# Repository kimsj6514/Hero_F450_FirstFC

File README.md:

# STM32F765 기반 커스텀 드론 비행 컨트롤러(FC) 개발

**현장 경험을 바탕으로 안정성과 신뢰성을 확보한 고성능 드론 FC를 직접 설계하고 개발하는 개인 프로젝트입니다.**

## 📖 프로젝트 소개
기성품 FC의 한계를 넘어, 특정 임무(정밀 비행, 안정적인 촬영 등)에 최적화된 드론을 개발하기 위해 시스템 아키텍처 설계부터 하드웨어 회로 설계, 펌웨어 개발까지 전 과정을 직접 수행합니다.

## ✨ 주요 기능
- [ ] IMU 센서(MPU-6050) 데이터 수신 및 처리
- [ ] Barometer 센서(BMP280)를 이용한 고도 추정
- [ ] PWM 신호를 이용한 BLDC 모터 제어
- [ ] (앞으로 개발할 기능들을 여기에 적어보세요)

## 🛠️ 기술 스택
- **MCU:** `STM32F765VI (ARM Cortex-M7)`
- **Language:** `C`, `C++`
- **Hardware Design:** `KiCad`
- **IDE:** `STM32CubeIDE`
- **Library:** `STM32 HAL Driver`

## 🏗️ 시스템 아키텍처

## 🔌 하드웨어 회로도

## 🚀 앞으로의 개발 계획
- [ ] FreeRTOS를 적용하여 멀티태스킹 환경 구축
- [ ] GPS 모듈을 연동하여 위치 기반 자율 비행 기능 구현
- [ ] PID 제어 알고리즘 튜닝을 통한 비행 안정성 향상

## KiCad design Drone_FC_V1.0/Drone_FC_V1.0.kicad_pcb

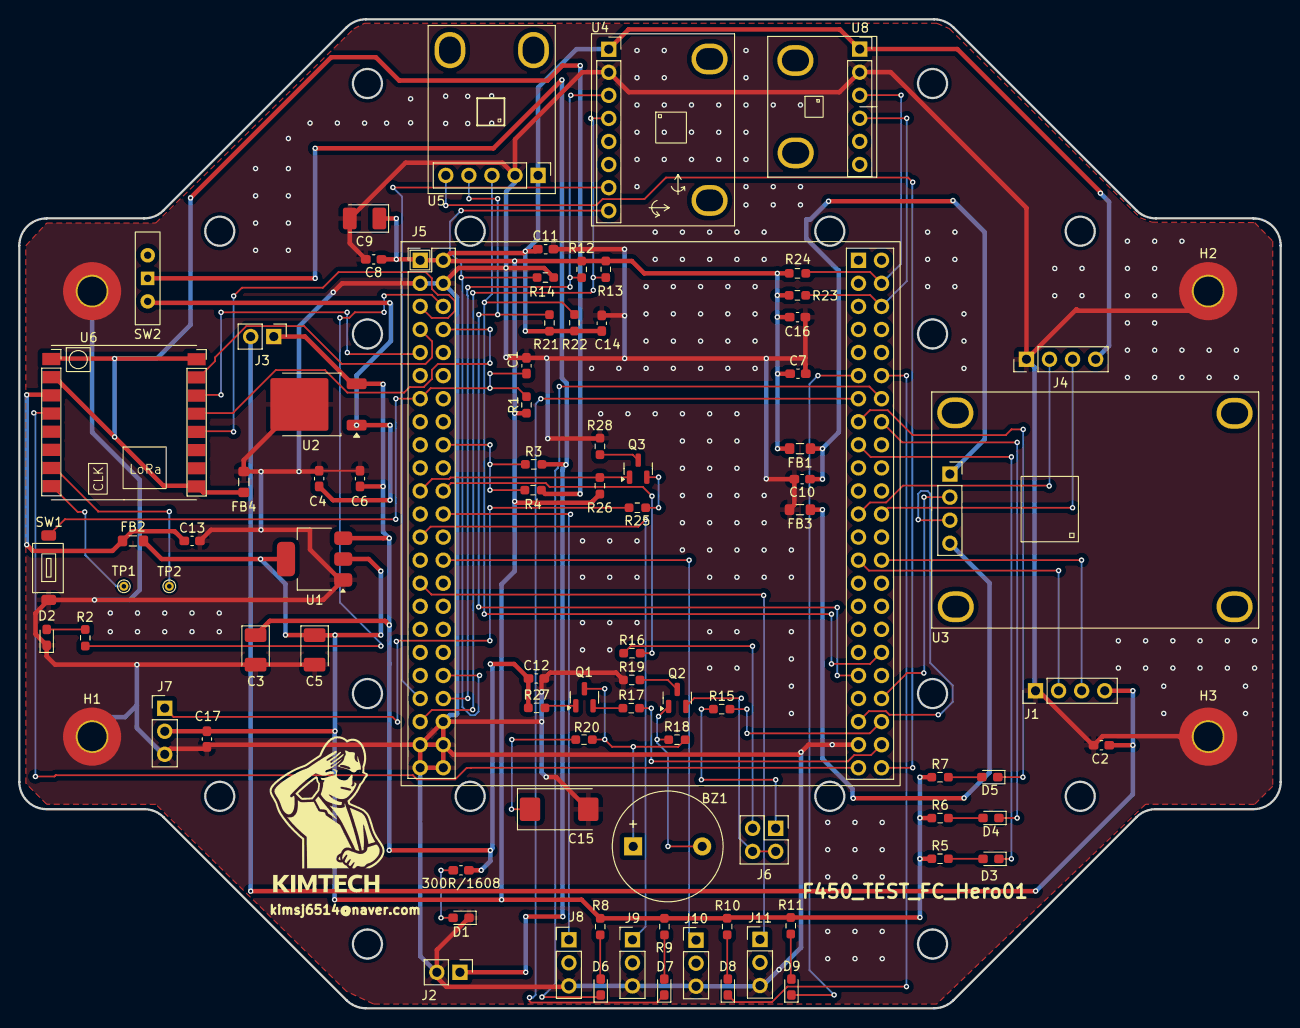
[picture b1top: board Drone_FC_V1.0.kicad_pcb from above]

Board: 2 copper layers, 138.9 x 108.9 mm, 89 parts (0 on the bottom side), 71 nets.

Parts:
300R/1608: R_Small_US; C_0603_1608Metric_Pad1.08x0.95mm_HandSolder
BZ1: Buzzer; Buzzer_12x9.5RM7.6
C1: 470nF/1608; C_0603_1608Metric_Pad1.08x0.95mm_HandSolder
C2, C6, C7, C8, C10, C11, C12, C13, C14, C16, C17: 100nF/1608; C_0603_1608Metric_Pad1.08x0.95mm_HandSolder
C3, C5, C9: 22uF/10V/TTB; CP_EIA-3528-21_Kemet-B_HandSolder
C4: 2.2uF/1608; C_0603_1608Metric_Pad1.08x0.95mm_HandSolder
C15: 220uF/10V/TTD; CP_EIA-7343-31_Kemet-D_HandSolder
D1: R_LED/1608; LED_0603_1608Metric_Pad1.05x0.95mm_HandSolder
D2, D8: GLED/1608; LED_0603_1608Metric_Pad1.05x0.95mm_HandSolder
D3, D4, D5: BLED/1608; LED_0603_1608Metric_Pad1.05x0.95mm_HandSolder
D6: RLED/1608; LED_0603_1608Metric_Pad1.05x0.95mm_HandSolder
D7: YLED/1608; LED_0603_1608Metric_Pad1.05x0.95mm_HandSolder
D9: WLED/1608; LED_0603_1608Metric_Pad1.05x0.95mm_HandSolder
FB1, FB2, FB3, FB4: FerriteBead/2012; L_0805_2012Metric_Pad1.05x1.20mm_HandSolder
H1, H2, H3, H4: MountingHole_Pad; MountingHole_3.2mm_M3_Pad_TopBottom
J1, J4: Conn_01x04(2.54mm); PinHeader_1x04_P2.54mm_Vertical
J2: Conn_01x02(2.54mm); PinHeader_1x02_P2.54mm_Vertical
J3: Conn_01x02; PinHeader_1x02_P2.54mm_Vertical
J5: LT_Conn_02x23_Odd_Even_2EA_Frame; LT_STM32F767VGT-23x2_Frame
J6: Conn_02x02_Odd_Even; PinHeader_2x02_P2.54mm_Vertical
J7, J8, J9, J10, J11: Conn_01x03(2.54mm); PinHeader_1x03_P2.54mm_Vertical
Q1, Q2, Q3: MMBT3904/SOT23; SOT-23
R1: 1MR/1608; R_0603_1608Metric_Pad0.98x0.95mm_HandSolder
R2, R5, R6, R7, R8, R9, R10, R11: 300R/1608; R_0603_1608Metric_Pad0.98x0.95mm_HandSolder
R3, R4: 510R(1.1KR)/1608F; R_0603_1608Metric_Pad0.98x0.95mm_HandSolder
R12, R13, R15, R16, R17, R21, R22, R23, R24, R25, R26: 1kR/1608; R_0603_1608Metric_Pad0.98x0.95mm_HandSolder
R14: 10kR/1608; R_0603_1608Metric_Pad0.98x0.95mm_HandSolder
R18, R20: 910R/1608; R_0603_1608Metric_Pad0.98x0.95mm_HandSolder
R19, R27, R28: 0R/1608; R_0603_1608Metric_Pad0.98x0.95mm_HandSolder
SW1: LT_SW_Push/TS1101; LT_TS-1101_SW
SW2: Slide_SW(MSL-1C2P); SW_Slide-03_Wuerth-WS-SLTV_10x2.5x6.4_P2.54mm
TP1, TP2: TestPoint_Small; TestPoint_THTPad_D1.0mm_Drill0.5mm
U1: AMS1117-3.3(SOT-223); SOT-223-3_TabPin2
U2: Hero_KIA7805_DPAK(TO252); TO-252-2
U3: Hero_NEO-6M(GY-GPS6MV2)_module; Hero_GY-NEO6MV2
U4: Hero_MPU6050_module; Hero_MPU6050_1x08_P2.54mm_Vertical
U5: Hero_GY-273_(HMC5883L)_module; Hero_gy273
U6: Hero_LoRa_Ra-02; Hero_RoLa_Ra-02_1x08_P2.00mm_Vertical
U8: Hero_BMP280_module; Hero_BMP280_1x06_P2.54mm_Vertical

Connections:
+3.3V: C5.1, C7.1, C8.1, C9.1, C11.1, C14.1, C16.1, C17.1, FB1.2, FB2.2, J4.4, J5.1, J5.2, J7.2, R1.1, R5.1, R6.1, R7.1, R8.1, R9.1, R10.1, R11.1, R12.2, R13.1, R21.2, R22.1, R23.2, R24.1, R26.1, U1.2 (VO), U4.1, U5.1, U8.1
+3.3VA_GPSR: C10.1, FB1.1, U3.1
+3.3VA_LoRa: C13.1, FB2.1, U6.3
+5V: 300R/1608.1, C3.1, C6.1, C12.1, J3.1, R27.1, U1.3 (VI), U2.3 (VO)
+5VP: C2.1, J1.4, J3.2
+Drone_PWR: C4.1, SW2.2 (C), U2.1 (VI)
+drone_batt: J2.1, R3.1, SW2.1 (B)
AGND1: FB3.1, U3.4
AGND2: FB4.1, R4.2, U6.1, U6.2, U6.9, U6.16
DGND: C1.2, C2.2, C3.2, C4.2, C5.2, C6.2, C7.2, C8.2, C9.2, C10.2, C11.2, C12.2, C13.2, C14.2, C15.2, C16.2, C17.2, D1.1 (K), D2.1 (K), FB3.2, FB4.2, H1.1, H2.1, H3.1, H4.1, J1.1, J2.2, J4.1, J5.3, J5.4, J5.42, J5.43, J5.44, J5.45, J5.46, J5.93, J7.3, J8.3, J9.3, J10.3, J11.3, R14.2, R19.1, R28.1, SW1.1, U1.1 (GND), U2.2 (GND), U4.2, U5.2, U8.2
unnamed: BZ1.1 (+), Q1.3 (E), R18.2, R20.2
unnamed: BZ1.2 (-), Q2.1 (C), R18.1
unnamed: C15.1, R20.1
unnamed: 300R/1608.2, D1.2 (A)
unnamed: D2.2 (A), R2.2
unnamed: D3.2 (A), R5.2
unnamed: D4.2 (A), R6.2
unnamed: D5.2 (A), R7.2
unnamed: D6.2 (A), R8.2
unnamed: D7.2 (A), R9.2
unnamed: D8.2 (A), R10.2
unnamed: D9.2 (A), R11.2
unnamed: J6.1, R15.1
unnamed: J6.2, J6.4, Q2.2 (B)
unnamed: J6.3, R16.1
unnamed: J7.1, R25.2
unnamed: Q1.2 (B), R17.1
unnamed: Q1.1 (C), R27.2
unnamed: Q2.3 (E), R19.2
unnamed: Q3.2 (B), R25.1
unnamed: Q3.3 (E), R28.2
unnamed: TP2.1, U6.7
unnamed: TP1.1, U6.8
PA0_ADC3_ch0: J5.18, R3.2, R4.1
PA3_USRART2_Rx: J5.21, Q3.1 (C), R26.2
PA4_DAC1_Output: J5.22, R16.2
PA6_TIM_LF_PWM: J5.24, J8.1
PA7_TIM_LR_PWM: J5.25, J9.1
PA9_US1_Tx: J1.3, J5.78
PA10_US1_Rx: J1.2, J5.77
PA13_SWDIO: J4.3, J5.74
PA14_SWCLK: J4.2, J5.73
PB0_TIM_RF_PWM: J5.28, J10.1
PB1_TIM_RR_PWM: J5.29, J11.1
PB7_I2C1_SDA: J5.56, R23.1, U8.4
PB8_I2C1_SCL: J5.54, R24.2, U8.3
PB10_I2C2_SCL: J5.40, R13.2, U4.3
PB11_I2C2_SDA: J5.41, R12.1, U4.4
PB12_HMC5883_DRDY: J5.96, U5.5
PB13_LoRa_RESET: J5.95, U6.4
PB14_BZ_ON: J5.94, R17.2
PB15_BZ_PULSE: J5.92, R15.2
PD1_Drone_RSSI1_BLED: D3.1 (K), J5.67 (Pin_17)
PD2_Drone_RSSI2_BLED: D4.1 (K), J5.66
PD3_Drone_RSSI3_BLED: D5.1 (K), J5.65
PD4_Drone_RLED: D6.1 (K), J5.64
PD5_Drone_YLED: D7.1 (K), J5.63
PD6_Drone_GLED: D8.1 (K), J5.62 (Pin_12)
PD7_Drone_WLED: D9.1 (K), J5.61
PD8_USART3_Tx: J5.91, U3.3
PD9_USART3_RX: J5.90, U3.2
PD12_I2C4_SCL: J5.86, R22.2, U5.3
PD13_I2C4_SDA: J5.87, R21.1, U5.4
PE2_SPI4_SCK: J5.5, U6.12
PE3_ALIVE: J5.6, R2.1
PE4_SPI4_NSS: J5.7, U6.15
PE5_SPI4_MISO: J5.8, U6.13
PE6_SPI4_MOSI: J5.9, U6.14
PE14_INT: J5.38, R14.1, U4.8
PE15_VDO: J5.39, U4.7
reset: C1.1, J5.13, R1.2, SW1.2

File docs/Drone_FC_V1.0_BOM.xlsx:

no | Reference | Value | Qty | U/ Price | Amount | (Delivery) | Maker | Vendor | Remark
 | 510R(1.1kR)/1608 | R_Small_US | 1
 | BZ1 | Buzzer | 1
 | C1 | 470nF/1608 | 1
 | C2,C6,C7,C8,C10,C11,C12,C13,C14,C16 | 100nF/1608 | 10
 | C3,C5,C9 | 22uF/10V/TTB | 3
 | C4 | 2.2uF/1608 | 1
 | C15 | 220uF/10V/TTD | 1
 | D1 | R_LED/1608 | 1
 | D2,D8 | GLED/1608 | 2
 | D3,D4,D5 | BLED/1608 | 3
 | D6 | RLED/1608 | 1
 | D7 | YLED/1608 | 1
 | D9 | WLED/1608 | 1
 | FB1,FB2 | FerriteBead/2012 | 2
 | J1,J4 | Conn_01x04(2.54mm) | 2
 | J2 | Conn_01x02(2.54mm) | 1
 | J3 | Conn_01x02 | 1
 | J5 | LT_Conn_02x23_Odd_Even_2EA_Frame | 1 | 60000
 | J6 | Conn_02x02_Odd_Even | 2 | 720
 | J7,J8,J9,J10,J11 | Conn_01x03(2.54mm) | 5
 | Q1,Q2,Q3 | MMBT3904/SOT23 | 3
 | R1 | 1MR/1608 | 1
 | R2,R5,R6,R7,R8,R9,R10,R11 | 300R/1608 | 8
 | R3,R4 | 510R(1.1KR)/1608F | 2
 | R12,R13,R15,R16,R17,R21,R22,R23,R24,R25,R26 | 1kR/1608 | 11
 | R14 | 10kR/1608 | 1
 | R18,R20 | 910R/1608 | 2
 | R19,R27,R28 | 0R/1608 | 3
 | SW1 | LT_SW_Push/TS1101 | 1
 | SW2 | Slide_SW(MSL-1C2P) | 1 | 150
 | TP1,TP2 | TestPoint_Small | 2
 | U1 | AMS1117-3.3(SOT-223) | 1 | 180
 | U2 | Kia7805AF-5.0V | 5 | 5000
 | U3 | Hero_NEO-6M(GY-GPS6MV2)_module | 1 | 4500
 | U4 | Hero_MPU6050_module | 1 | 3000
 | U5 | GY-273_(HMC5883L)_module | 1 | 2500
 | U6 | Hero_LoRa_Ra-02 | 1 | 6000
 | U7 | Hero_BMP280_module | 1 | 2000
 |  | 충전기
 |  | XT60 커넥터 세트
 |  | 드론 교육용 세트 F450

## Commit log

2025-09-15 FC 펌웨어 프로젝트 초기 파일 추가
2025-09-15 프로젝트 폴더 구조 정리
